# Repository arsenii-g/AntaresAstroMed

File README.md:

# AstroMed · Team Antares · NASA Space Apps 2026

An astronaut health monitoring prototype that brings sensor readings, guided daily checks, and explainable risk assessments together in one dashboard.

**Live demo:** [arsenii-g.github.io/AntaresAstroMed](https://arsenii-g.github.io/AntaresAstroMed/). Open the console from the landing page. The online version has no API behind it, so it replays a session recorded from the AstroMed API and the two-board simulator; daily checks are not saved there.

## About

AstroMed is developed by **Team Antares** for the NASA Space Apps 2026 challenge, *Create Health Monitoring Software for Astronauts on Space Missions*.

When medical support from Earth is delayed or unavailable, astronauts need a clear view of their condition and practical next steps. AstroMed connects an Arduino UNO and ESP32 sensor station to a web application that guides daily checks, explains risk alerts, and records exercise with physical sensors. Its goal is to support crew autonomy through understandable information and guidance.

This is the final hackathon version. The `main` branch contains the integrated application, firmware, simulator, and hardware design.

## What it does

- Collects crew and cabin telemetry, RFID check-ins, inactivity events, and exercise repetitions.
- Guides manual checks for blood pressure, fasting glucose, and mood.
- Evaluates four systems: cardiovascular, neurobehavioral, musculoskeletal, and cabin environment.
- Displays live readings, a clickable body view, explanations, recommendations, and trendlines with their measured data points.
- Prepares a summary for medical support on Earth when the overall risk reaches red.
- Includes firmware, a configurable two-ESP32 simulator, and KiCad schematic, PCB, BOM, and fabrication files.

## Run the API and web application

Use **Python 3.11 or later**. From the repository root, create a virtual environment:

```bash
python -m venv .venv
```

Activate it on macOS or Linux:

```bash
source .venv/bin/activate
```

On Windows PowerShell:

```powershell
.\.venv\Scripts\Activate.ps1
```

Install the dependencies and start the application:

```bash
python -m pip install -r requirements.txt
python -m uvicorn api.main:app --env-file .env.example --host 0.0.0.0 --port 8000
```

Open the [landing page](http://localhost:8000) or the [crew console](http://localhost:8000/console.html). The API also serves the frontend files, so no separate web server or frontend build is required. To connect from another device on the same network, replace `localhost` with the computer's local IP address.

The supplied [`.env.example`](.env.example) enables `ASTROMED_DEMO=1`, which triggers the inactivity alert after 30 seconds, matching the current firmware. Copy its settings to `.env` and start with `--env-file .env` to customize them.

Configuration uses `ASTROMED_API_KEY`, `ASTROMED_CORS_ORIGINS`, and the optional `ASTROMED_DATABASE_URL`. Legacy `SPACEHEALTH_*` names and an existing `spacehealth.db` are still honored; see [`api/README.md`](api/README.md) for details.

The default API key and the CORS `*` setting in `.env.example` are demo settings only; see the security notes in [`api/README.md`](api/README.md) before exposing the API beyond a trusted network.

The ESP32 must use the same API key as the backend and the computer's address in `API_BASE`. GET requests and the dashboard's manual check endpoint do not require an API key. See the [firmware setup and wiring guide](firmware/README.md) for the physical device.

## Try it with the simulator

With the API running, open another terminal, activate the virtual environment, and run:

```bash
python -m simulator.simulate
```

The simulator represents **two ESP32 devices, one per crew member**. Configure each crew member's target level in [`simulator/config.json`](simulator/config.json), or override it from the command line:

```bash
python -m simulator.simulate --level F3786E09=1 --level 336F8312=3
python -m simulator.simulate --mode normal
```

Manual checks are entered through the console's *Daily check* view. The simulator sends the same message format as the physical station; the API and risk engine calculate the assessments and trendlines. See the [simulator guide](simulator/README.md) for configuration and operating modes.

On Windows, after creating the virtual environment, [`start-demo.bat`](start-demo.bat) starts the API and simulator in separate windows.

## How it works

```mermaid
flowchart LR
    Sensors --> UNO[Arduino UNO]
    UNO -->|UART JSON| ESP[ESP32]
    ESP -->|Wi-Fi HTTP POST| API[FastAPI + SQLite]
    Web[AstroMed dashboard] -->|Daily check| API
    API -->|Local evaluate call| Risk[Rules engine]
    Risk -->|Assessment| API
    API -->|HTTP GET + WebSocket| Web
```

The physical station and simulator send telemetry every **2 seconds**. The API preserves the original UTC timestamps, handles duplicate retries, stores the messages in SQLite, and calls the risk engine in the same Python process.

The engine uses configurable, explainable rules in [`risk/thresholds.json`](risk/thresholds.json). It assigns levels from **0 (green)** to **3 (red)**, with a reason for each alert. Missing readings remain `null`: they mean **no data**, never a normal measurement.

The console follows RFID check-ins, allows manual crew selection, and shows the readings, system status, actions, and trendlines returned by the engine. The Earth summary is prepared for review and copying; it is not automatically sent to an external service.

### Hardware

An Arduino UNO reads the sensors and an ESP32 forwards the data over Wi-Fi. The custom PCB that combines them is designed in KiCad; see the [hardware guide](hardware/README.md).

## Repository structure

| Directory | Contents | Owner |
|---|---|---|
| `contracts/` | JSON examples and shared Pydantic models | Team Antares |
| `firmware/` | Arduino UNO sensor acquisition and ESP32 Wi-Fi gateway | [0xtherin](https://github.com/0xtherin) |
| `hardware/` | KiCad schematic, PCB layout, fabrication files, and BOM | Team Antares |
| `risk/` | Risk engine and `thresholds.json` | [arsenii-g](https://github.com/arsenii-g) |
| `simulator/` | Two simulated ESP32 devices with configurable levels | [arsenii-g](https://github.com/arsenii-g) |
| `api/` | FastAPI endpoints, SQLite persistence, and WebSocket | [arsenii-g](https://github.com/arsenii-g), [Pought79](https://github.com/Pought79) |
| `frontend/web/` | AstroMed console, clickable body, daily checks, and charts | [Pought79](https://github.com/Pought79) |

## Data contracts

| Contract | Flow | Interface | Owner |
|---|---|---|---|
| ① | Telemetry and events: ESP32 → API | `POST /api/v1/telemetry`, `POST /api/v1/events` | 0xtherin |
| ② | Manual check: frontend → API | `POST /api/v1/checks` | Pought79 |
| ③ | Risk assessment: engine → API | `evaluate(...)` | arsenii-g |
| ④ | Latest state and live updates: API → frontend | `GET /api/v1/crew/{crew_id}/latest`, WebSocket | arsenii-g, Pought79 |

All dates use UTC in ISO 8601 format. The API imports the engine directly:

```python
from datetime import datetime, timezone
from risk import evaluate

assessment = evaluate(
    telemetry=telemetry_messages,
    events=event_messages,
    manual_checks=manual_check_messages,
    now=datetime.now(timezone.utc),
)
```

Each input is a list of JSON message dictionaries for a **single `crew_id`**. The engine returns the assessment described in [`contracts/assessment.example.json`](contracts/assessment.example.json). Crew names and roles are provided by the API or frontend.

The API supplies telemetry from the last minute and events and manual checks from the last seven days. See the [risk engine guide](risk/README.md) for evaluation rules and trendlines, the [contract definitions](contracts/README.md) for message formats, and the [API guide](api/README.md) for endpoints.

## Run the checks

Install the development dependencies and run the Python suite:

```bash
python -m pip install -r requirements-dev.txt
python -m pytest -q
```

Frontend tests require **Node.js 20 or later**, with no additional packages:

```bash
node --test frontend/web/tests/*.test.js
```

## Final version and contributions

Use [`main`](https://github.com/arsenii-g/AntaresAstroMed/tree/main) for the final Team Antares submission. Historical feature branches are retained as development history; the integrated console served by the API is in `frontend/web/`.

For future changes, open a pull request against `main`. Changes to a data contract should be reviewed by both the producer and consumer of that data.

## Credits

AstroMed builds on the following third-party software, data, and standards.

- **Backend:** [FastAPI](https://fastapi.tiangolo.com/), [Uvicorn](https://www.uvicorn.org/), [SQLAlchemy](https://www.sqlalchemy.org/), and [Pydantic](https://docs.pydantic.dev/) (see `requirements.txt`). Tests use [pytest](https://pytest.org/) and [HTTPX](https://www.python-httpx.org/).
- **Firmware:** the Arduino and ESP32 cores, the [MFRC522](https://github.com/miguelbalboa/rfid) library for the RFID reader, and [ArduinoJson](https://arduinojson.org/).
- **Hardware design:** [KiCad](https://www.kicad.org/).
- **Frontend:** [Google Fonts](https://fonts.google.com/): Sora, Inter, and JetBrains Mono.
- **Standards and guidelines behind `risk/thresholds.json`:** NASA-STD-3001 (vols. 1 and 2), American Heart Association (AHA/ACC) blood pressure and heart rate guidance, American Diabetes Association (ADA) Standards of Care, and NOAA/NWS heat index tables.
- **Thermistor calibration:** the Steinhart-Hart coefficients in `firmware/tests/thermistor_test/` come from the Elegoo sensor kit tutorial.

## Use of AI (Super Intelligence tools)

As allowed by the NASA Space Apps rules, Team Antares used AI assistants, including Anthropic's Claude, during the hackathon. We disclose that use here.

- **Code:** AI-assisted. Parts of the API, risk engine, simulator, web console, firmware and tests were written, debugged or reviewed with AI help. The team designed the system, built and wired the hardware, and ran and checked the code against the real sensor station and the test suite.
- **Writing and translation:** AI-assisted. The documentation was drafted, edited and translated from Spanish to English with AI help.
- **Presentation and video:** AI-assisted. The motion graphics in the demo video were generated with AI-written code. The video carries a visible "SI-generated" watermark. Its footage of the breadboard and its voice-over are the team's own.
- **Hardware design files:** AI-assisted. The KiCad schematic and PCB files were prepared with AI help and checked with KiCad's electrical and design rule checks.
- **Not AI-generated:** the physical prototype, its wiring and the sensor readings recorded from it.

No NASA logos or other NASA branding were generated or modified.

## Limitations

AstroMed is an educational prototype built with a sensor kit. Its measurements are not medical-grade, and its thresholds are for demonstration rather than clinical use. Sources and assumptions are documented in `risk/thresholds.json`.

Sleep monitoring and respiration measurement are outside the current scope. The HC-SR04 is used to count push-ups. The four assessed systems are cardiovascular, neurobehavioral, musculoskeletal, and cabin environment.

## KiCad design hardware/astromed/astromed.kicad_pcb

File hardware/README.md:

# AstroMed · Team Antares: Arduino UNO + ESP32 shield

Schematic and PCB for the AstroMed shield, a board that replaces the breadboard prototype. It sits on top of an **Arduino UNO R3**, carries an **ESP32 DevKit V1 (30-pin, CP2102)** in female headers, and provides connectors for every sensor.

Pin assignments follow [`firmware/uno_sensors/config.h`](../firmware/uno_sensors/config.h), [`firmware/esp32_gateway/config.example.h`](../firmware/esp32_gateway/config.example.h) and [`firmware/README.md`](../firmware/README.md). Any pin change on the PCB must also be made in `config.h`.

The PIR sensor, the sleep sensors and the HC-SR04 respiration measurement were removed from the project and are not part of this design.

## Files

| File | Description |
|---|---|
| `schematic.pdf` | Schematic, A3 PDF |
| `schematic.png` | Schematic, PNG at 200 dpi |
| `bom.csv` | Bill of materials exported from KiCad |
| `astromed/astromed.kicad_pro` | KiCad project file |
| `astromed/astromed.kicad_sch` | Schematic (KiCad 10 format) |
| `astromed/astromed.net` | Netlist (KiCad S-expression) |
| `astromed/erc.rpt` | Electrical rules check report |
| `astromed/astromed.kicad_pcb` | PCB layout |
| `astromed/astromed.kicad_dru` | Custom design rules (see [PCB](#pcb)) |
| `astromed/drc.rpt` | Design rules check report, including schematic parity |
| `pcb_top.png`, `pcb_bottom.png`, `pcb_3d.png` | 3D renders of the board |
| `kicad_pcb_editor.png`, `kicad_3d_bottom.png` | Screenshots of the KiCad PCB editor and 3D viewer (bottom side) |
| `gerbers/` | Gerber and Excellon drill files |
| `astromed_gerbers.zip` | Same files zipped, ready to upload to a PCB manufacturer |

- **KiCad version:** 10.0.8. Files saved by KiCad 10 cannot be opened in KiCad 8 or 9.
- **Libraries:** only the standard KiCad libraries are used (`Device`, `Connector_Generic`, `MCU_Module`, `Switch`, `Jumper`, `power`). Symbols are also embedded in the `.kicad_sch` file.
- **Schematic changes:** after editing the schematic, run *Tools → Update PCB from Schematic* (F8) in the PCB editor. Footprints are linked to their symbols, so existing placement and routing are kept.

## Design notes

- **Shield form factor.** `A1` uses the `Module:Arduino_UNO_R3_WithMountingHoles` footprint, which provides the UNO outline, mounting holes and header positions. Use stackable headers (1x10, 2x 1x8 and 1x6).
- **Sensors that move use JST-XH connectors.** The HC-SR04 (on the floor, push-ups), the tilt switch (worn by the crew member), the NTC (wrist) and the pulse finger clip connect through latching 2.5 mm JST-XH connectors (`J2`, `J3`, `J6`, `J7`), so cables do not pull out during use.
- **Static modules plug into the board.** The DHT11 (`J4`) and the DS1307 RTC (`J5`) plug into female sockets, with no cables. The RC522 (`J1`) stays on a 1x08 male header and is wired to the reader, which must sit on an accessible face of the enclosure.
- **ESP32 on 1x15 female headers, with two positions for the right row.** KiCad has no symbol for the DevKit V1. Pin 1 of each header is at the antenna end. The right row can be fitted at 25.4 mm (`J9`, row A, default) or 22.86 mm (`J11`, row B, marked DNP) from the left row (`J8`), because 30-pin DevKit V1 clones use either spacing. Measure the board and solder the socket in the matching row only.
- **Pulse sensor on a 4-pin connector (`J7`).** The LED and LDR face each other across the fingertip, so they are mounted in an external finger clip. The 220 Ω and 10 kΩ resistors are on the PCB. The firmware measures the pulse with this LED and LDR pair over a 10 s window (`PIN_PULSE_LED`, `PIN_PULSE_LDR` and `PULSE_WINDOW_MS` in `config.h`).
- **Off-board parts.** `TH1` (NTC), `D1` (LED), `R6` (LDR) and `SW2` (tilt switch) are drawn to show the complete circuit and are listed in the BOM. They are marked `on_board = no` (field *Mounting*), so they have no footprint and are not transferred to the PCB. Each one is wired to its connector.
- **Push button `SW1`.** 6 mm tactile switch mounted on the board. It is optional.
- **Spare pins.** D2, A2 and A3 are routed to header `J10` together with 5V and GND.

## Connections

### Arduino UNO

| UNO pin | Net | Connects to |
|---|---|---|
| D1 (TX) | `UNO_TX` | R4 1 kΩ to `ESP_RX2` (level divider to the ESP32) |
| D2 | `D2_SPARE` | J10-1 (spare) |
| D3 | `D3_TILT` | J3-1, SW-520D tilt switch to GND (internal pull-up) |
| D4 | `D4_DHT` | J4-1 (DHT11 data) |
| D5 | `D5_US_TRIG` | J2-2 (HC-SR04 TRIG) |
| D6 | `D6_US_ECHO` | J2-3 (HC-SR04 ECHO) |
| D7 | `D7_BTN` | SW1 to GND (internal pull-up) |
| D8 | `D8_PULSE_LED` | R2 220 Ω to `PULSE_LED_A`, J7-1 (LED anode) |
| D9 | `D9_RFID_RST` | J1-7 (RC522 RST) |
| D10 | `D10_RFID_SS` | J1-1 (RC522 SDA/SS) |
| D11 | `D11_SPI_MOSI` | J1-3 (MOSI) |
| D12 | `D12_SPI_MISO` | J1-4 (MISO) |
| D13 | `D13_SPI_SCK` | J1-2 (SCK) |
| A0 | `A0_NTC` | J6-2 (NTC to 5V), R1 10 kΩ to GND |
| A1 | `A1_PULSE_LDR` | J7-4 (LDR to 5V), R3 10 kΩ to GND |
| A2 | `A2_SPARE` | J10-2 (spare) |
| A3 | `A3_SPARE` | J10-3 (spare) |
| A4 (SDA) | `A4_I2C_SDA` | J5-3 (DS1307 SDA) |
| A5 (SCL) | `A5_I2C_SCL` | J5-4 (DS1307 SCL) |
| 5V | `+5V` | J2-1, J4-2, J5-1, J6-1, J7-3, J10-4, JP1-1 |
| 3.3V | `+3V3` | J1-8 only (RC522 supply) |
| GND (x3) | `GND` | Common ground, including the ESP32 |

Not connected: D0/RX (used by USB for programming), VIN, RESET, IOREF, AREF, and the SDA/SCL pins next to AREF (internally the same as A4/A5).

### Connectors

| Ref | Function | Pin 1 | Pin 2 | Pin 3 | Pin 4 | Pin 5 | Pin 6 | Pin 7 | Pin 8 |
|---|---|---|---|---|---|---|---|---|---|
| J1 (1x08) | RC522 | SDA (D10) | SCK (D13) | MOSI (D11) | MISO (D12) | IRQ (NC) | GND | RST (D9) | 3.3V |
| J2 (JST-XH 4) | HC-SR04 (floor, push-ups) | VCC 5V | TRIG (D5) | ECHO (D6) | GND | | | | |
| J3 (JST-XH 2) | SW-520D (worn by crew member) | D3 | GND | | | | | | |
| J4 (socket 1x03) | DHT11 module | DATA (D4) | 5V | GND | | | | | |
| J5 (socket 1x04) | DS1307 RTC | VCC 5V | GND | SDA (A4) | SCL (A5) | | | | |
| J6 (JST-XH 2) | 10k NTC (skin contact) | 5V | A0 | | | | | | |
| J7 (JST-XH 4) | Pulse finger clip | LED anode (after 220 Ω) | LED cathode (GND) | LDR to 5V | LDR to A1 | | | | |
| J10 (1x05) | Spare pins | D2 | A2 | A3 | 5V | GND | | | |
| JP1 (1x02 + jumper) | ESP32 power | UNO 5V | ESP32 VIN | | | | | | |

The DHT11 and RTC sockets follow the pin order above, which may not match every module: pinouts vary between manufacturers. Check the module before plugging it in. If the order differs, connect it with jumper wires by pin name instead.

### ESP32 DevKit V1

J8 is the left row and J9 the right row (row A, 25.4 mm), with pin 1 at the antenna end. J11 (row B, 22.86 mm) has the same pinout as J9.

| Pin | J8 | Connection | J9 | Connection |
|---|---|---|---|---|
| 1 | EN | NC | D23 | NC |
| 2 | VP (GPIO36) | NC | D22 | NC |
| 3 | VN (GPIO39) | NC | TX0 | NC |
| 4 | D34 | NC | RX0 | NC |
| 5 | D35 | NC | D21 | NC |
| 6 | D32 | NC | D19 | NC |
| 7 | D33 | NC | D18 | NC |
| 8 | D25 | NC | D5 | NC |
| 9 | D26 | NC | TX2 (GPIO17) | NC |
| 10 | D27 | NC | **RX2 (GPIO16)** | **`ESP_RX2`** |
| 11 | D14 | NC | D4 | NC |
| 12 | D12 | NC | D2 | NC (on-board blue LED) |
| 13 | D13 | NC | D15 | NC |
| 14 | **GND** | **GND** | **GND** | **GND** |
| 15 | **VIN** | **`ESP_VIN`** (JP1) | 3V3 | NC |

### UART link, UNO to ESP32 (115200 baud)

```
UNO D1 (TX) ──R4 1k──┬── ESP32 GPIO16 (RX2)     5 V × 2k/(1k+2k) = 3.33 V
                     └──R5 2k── GND
```

- The link is one-way. ESP32 TX2 is not connected.
- With JP1 fitted, the ESP32 is powered from the UNO 5V rail through VIN. With JP1 removed, the ESP32 is powered from its own USB port. Ground is shared in both cases.
- With JP1 removed and the ESP32 unpowered, the divider still applies about 3.3 V to GPIO16. This does not damage the board, but both boards should normally be powered together.

### Analog circuits

- **Body temperature:** 5V, NTC (via J6, on the crew member's wrist), A0, R1 10 kΩ, GND.
- **Pulse emitter:** D8, R2 220 Ω, red LED (via J7), GND.
- **Pulse receiver:** 5V, LDR (via J7), A1, R3 10 kΩ, GND.

## Bill of materials

| Ref | Qty | Part | KiCad footprint | Mounting |
|---|---|---|---|---|
| A1 | 1 | Arduino UNO R3 (host board) | `Module:Arduino_UNO_R3_WithMountingHoles` | Long-pin or stackable headers |
| - | 1 | ESP32 DevKit V1, 30-pin, CP2102 | (on J8/J9) | Plugged into headers |
| - | 1 set | Stackable headers for the UNO: 1x10, 2x 1x8, 1x6 | (on A1) | On board |
| J8, J9 | 2 | Female header 1x15, 2.54 mm | `Connector_PinSocket_2.54mm:PinSocket_1x15_P2.54mm_Vertical` | On board |
| J11 | - | Female header 1x15, 2.54 mm, instead of J9 for 22.86 mm boards | Same as above | DNP |
| J1 | 1 | Male header 1x08, 2.54 mm (RC522) | `Connector_PinHeader_2.54mm:PinHeader_1x08_P2.54mm_Vertical` | On board |
| J2, J7 | 2 | JST-XH B4B-XH-A, 4 pins (HC-SR04, pulse) | `Connector_JST:JST_XH_B4B-XH-A_1x04_P2.50mm_Vertical` | On board |
| J3, J6 | 2 | JST-XH B2B-XH-A, 2 pins (tilt, NTC) | `Connector_JST:JST_XH_B2B-XH-A_1x02_P2.50mm_Vertical` | On board |
| - | 2 + 2 | JST-XH housings XHP-4 and XHP-2, with SXH-001T-P0.6 crimp terminals | - | Cable side |
| J4 | 1 | Female socket 1x03, 2.54 mm (DHT11) | `Connector_PinSocket_2.54mm:PinSocket_1x03_P2.54mm_Vertical` | On board |
| J5 | 1 | Female socket 1x04, 2.54 mm (RTC) | `Connector_PinSocket_2.54mm:PinSocket_1x04_P2.54mm_Vertical` | On board |
| J10 | 1 | Male header 1x05, 2.54 mm (spare pins) | `Connector_PinHeader_2.54mm:PinHeader_1x05_P2.54mm_Vertical` | On board |
| JP1 | 1 | Male header 1x02 with jumper | `Connector_PinHeader_2.54mm:PinHeader_1x02_P2.54mm_Vertical` | On board |
| R1, R3 | 2 | Resistor 10 kΩ, 1/4 W | `Resistor_THT:R_Axial_DIN0207_L6.3mm_D2.5mm_P10.16mm_Horizontal` | On board |
| R2 | 1 | Resistor 220 Ω, 1/4 W | Same as above | On board |
| R4 | 1 | Resistor 1 kΩ, 1/4 W | Same as above | On board |
| R5 | 1 | Resistor 2 kΩ, 1/4 W (2.2 kΩ also acceptable, 3.4 V) | Same as above | On board |
| SW1 | 1 | Tactile switch 6x6 mm (optional) | `Button_Switch_THT:SW_PUSH_6mm` | On board |
| TH1 | 1 | NTC thermistor 10 kΩ | - | Off board, wired to J6 |
| D1 | 1 | Red LED 5 mm | - | Off board, wired to J7 |
| R6 | 1 | Photoresistor (LDR, e.g. GL5528) | - | Off board, wired to J7 |
| SW2 | 1 | SW-520D tilt switch | - | Off board, wired to J3 |
| - | 1 | RC522 module with cards | - | Wired to J1 |
| - | 1 | HC-SR04 module | - | Wired to J2 (floor-mounted) |
| - | 1 | DHT11 module (3-pin) | - | Plugged into J4 |
| - | 1 | DS1307 RTC module | - | Plugged into J5 |

The KiCad export is in `bom.csv`.

## PCB

| Parameter | Value |
|---|---|
| Size | 104.14 x 67.31 mm (UNO outline plus a 35.56 mm extension for the ESP32 and a 13.97 mm connector strip) |
| Layers | 2, 1.6 mm FR-4, all parts through-hole |
| Tracks | 0.3 mm signals, 0.5 mm for +5V, +3V3 and ESP_VIN |
| Clearance | 0.2 mm minimum, 0.6 mm from tracks to the board edge |
| Vias | 0.7 mm pad, 0.35 mm drill (10 in total) |
| Ground | GND pour on both layers |
| Mounting | The four UNO holes plus one M3 hole (`H1`) under the overhanging corner |

Layout:

- The UNO headers are at their standard positions on the left. The ESP32 sits on the right extension with its USB connector towards the bottom edge. Its antenna overhangs the top edge, over a copper keepout area.
- All cable connectors are in a row along the bottom edge, labelled on the silkscreen (`J4 DHT11`, `J1 RC522`, `J2 HC-SR04`, `J3 TILT`, `J6 NTC`, `J7 PULSE`). The DHT11 is in the far corner, away from the heat of the ESP32.
- The divider resistors R4 and R5 sit under the ESP32, between its two rows. With the socket height, they fit under the module.
- The UNO USB-B connector is close to the underside of the shield. Put a piece of insulating tape on top of it before stacking the boards.

`astromed.kicad_dru` adds five rules for situations that are intended in this design: shield parts inside the UNO courtyard, the overlapping J9/J11 rows and their silkscreen, the UNO outline reaching past the board edge, and GND pads with a single thermal spoke on the top layer, which are still fully connected on the bottom layer.

Screenshots from KiCad:

To order the board, upload `astromed_gerbers.zip`. Default options are fine: 2 layers, 1.6 mm, 1 oz copper, any solder mask colour.

## Verification

- **ERC:** `kicad-cli sch erc --severity-all` reports 0 errors and 0 warnings. A single `PWR_FLAG` is placed on GND; +5V and 3V3 are driven by the UNO power pins.
- **Netlist:** all 25 named nets were checked against the connection tables above, including off-board parts.
- **Footprints:** every footprint in the netlist loads in KiCad 10.0.8 `pcbnew`, and pad counts match the symbol pin counts (32 for the UNO).
- **DRC:** `kicad-cli pcb drc --schematic-parity --severity-all --refill-zones` reports 0 violations, 0 unconnected pads and 0 schematic parity errors.
- **Not yet done:** measurement of the ESP32 row spacing (choose J9 or J11), and fabrication and testing of a board.

## Regenerating outputs

From `hardware/`, with `kicad-cli` from KiCad 10:

```bash
kicad-cli sch erc --severity-all -o astromed/erc.rpt astromed/astromed.kicad_sch
kicad-cli sch export netlist -o astromed/astromed.net astromed/astromed.kicad_sch
kicad-cli sch export bom --fields 'Reference,Value,Footprint,${QUANTITY},Mounting,${DNP}' --labels 'Reference,Value,Footprint,Quantity,Mounting,DNP' --group-by Value,Footprint --ref-range-delimiter '' -o bom.csv astromed/astromed.kicad_sch
kicad-cli sch export pdf -o schematic.pdf astromed/astromed.kicad_sch
pdftoppm -png -r 200 -singlefile schematic.pdf schematic
kicad-cli pcb drc --schematic-parity --severity-all --refill-zones --save-board -o astromed/drc.rpt astromed/astromed.kicad_pcb
kicad-cli pcb export gerbers --no-protel-ext -l F.Cu,B.Cu,F.Silkscreen,B.Silkscreen,F.Mask,B.Mask,Edge.Cuts -o gerbers/ astromed/astromed.kicad_pcb
kicad-cli pcb export drill --excellon-separate-th -o gerbers/ astromed/astromed.kicad_pcb
(cd gerbers && zip ../astromed_gerbers.zip *)
kicad-cli pcb render --side top --quality high -o pcb_top.png astromed/astromed.kicad_pcb
```

When using the AppImage, run `kicad-cli` as `./kicad.appimage kicad-cli <arguments>`.

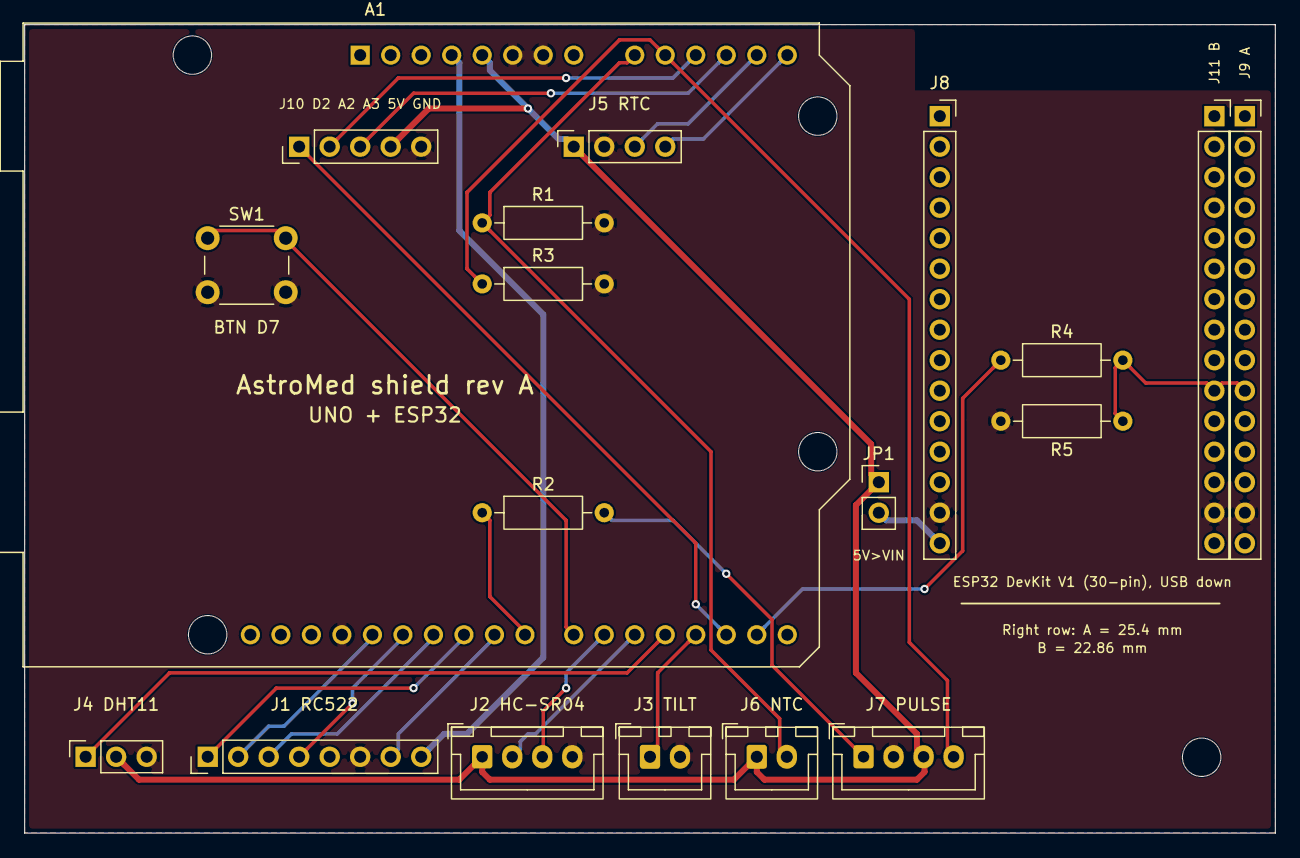
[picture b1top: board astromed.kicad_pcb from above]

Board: 2 copper layers, 104.1 x 67.3 mm, 20 parts (0 on the bottom side), 25 nets.

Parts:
A1: Arduino_UNO_R3; Arduino_UNO_R3_WithMountingHoles
H1: M3; MountingHole_3.2mm_M3
J1: RC522; PinHeader_1x08_P2.54mm_Vertical
J2: HC-SR04; JST_XH_B4B-XH-A_1x04_P2.50mm_Vertical
J3: TILT; JST_XH_B2B-XH-A_1x02_P2.50mm_Vertical
J4: DHT11; PinSocket_1x03_P2.54mm_Vertical
J5: RTC_DS1307; PinSocket_1x04_P2.54mm_Vertical
J6: NTC; JST_XH_B2B-XH-A_1x02_P2.50mm_Vertical
J7: PULSE; JST_XH_B4B-XH-A_1x04_P2.50mm_Vertical
J8: ESP32_LEFT; PinSocket_1x15_P2.54mm_Vertical
J9: ESP32_RIGHT; PinSocket_1x15_P2.54mm_Vertical
J10: SPARE; PinHeader_1x05_P2.54mm_Vertical
J11: ESP32_RIGHT_ALT; PinSocket_1x15_P2.54mm_Vertical
JP1: 5V->VIN; PinHeader_1x02_P2.54mm_Vertical
R1, R3: 10k; R_Axial_DIN0207_L6.3mm_D2.5mm_P10.16mm_Horizontal
R2: 220; R_Axial_DIN0207_L6.3mm_D2.5mm_P10.16mm_Horizontal
R4: 1k; R_Axial_DIN0207_L6.3mm_D2.5mm_P10.16mm_Horizontal
R5: 2k; R_Axial_DIN0207_L6.3mm_D2.5mm_P10.16mm_Horizontal
SW1: Push button 6 mm; SW_PUSH_6mm

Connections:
+3V3: A1.4, J1.8
+5V: A1.5, J2.1, J4.2, J5.1, J6.1, J7.3, J10.4, JP1.1
A0_NTC: A1.9, J6.2, R1.1
A1_PULSE_LDR: A1.10, J7.4, R3.1
A2_SPARE: A1.11, J10.2
A3_SPARE: A1.12, J10.3
A4_I2C_SDA: A1.13, J5.3
A5_I2C_SCL: A1.14, J5.4
D2_SPARE: A1.17, J10.1
D3_TILT: A1.18, J3.1
D4_DHT: A1.19, J4.1
D5_US_TRIG: A1.20, J2.2
D6_US_ECHO: A1.21, J2.3
D7_BTN: A1.22, SW1.1
D8_PULSE_LED: A1.23, R2.1
D9_RFID_RST: A1.24, J1.7
D10_RFID_SS: A1.25, J1.1
D11_SPI_MOSI: A1.26, J1.3
D12_SPI_MISO: A1.27, J1.4
D13_SPI_SCK: A1.28, J1.2
ESP_RX2: J9.10, J11.10, R4.2, R5.1
ESP_VIN: J8.15, JP1.2
GND: A1.6, A1.7, A1.29, J1.6, J2.4, J3.2, J4.3, J5.2, J7.2, J8.14, J9.14, J10.5, J11.14, R1.2, R3.2, R5.2, SW1.2
PULSE_LED_A: J7.1, R2.2
UNO_TX: A1.16, R4.1

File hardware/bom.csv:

"Reference","Value","Footprint","Quantity","Mounting","DNP"
"A1","Arduino_UNO_R3","Module:Arduino_UNO_R3_WithMountingHoles","1","",""
"D1","Red LED 5 mm","","1","Off board (wired to its connector)",""
"J1","RC522","Connector_PinHeader_2.54mm:PinHeader_1x08_P2.54mm_Vertical","1","",""
"J2","HC-SR04","Connector_JST:JST_XH_B4B-XH-A_1x04_P2.50mm_Vertical","1","",""
"J3","TILT","Connector_JST:JST_XH_B2B-XH-A_1x02_P2.50mm_Vertical","1","",""
"J4","DHT11","Connector_PinSocket_2.54mm:PinSocket_1x03_P2.54mm_Vertical","1","",""
"J5","RTC_DS1307","Connector_PinSocket_2.54mm:PinSocket_1x04_P2.54mm_Vertical","1","",""
"J6","NTC","Connector_JST:JST_XH_B2B-XH-A_1x02_P2.50mm_Vertical","1","",""
"J7","PULSE","Connector_JST:JST_XH_B4B-XH-A_1x04_P2.50mm_Vertical","1","",""
"J8","ESP32_LEFT","Connector_PinSocket_2.54mm:PinSocket_1x15_P2.54mm_Vertical","1","",""
"J9","ESP32_RIGHT","Connector_PinSocket_2.54mm:PinSocket_1x15_P2.54mm_Vertical","1","",""
"J10","SPARE","Connector_PinHeader_2.54mm:PinHeader_1x05_P2.54mm_Vertical","1","",""
"J11","ESP32_RIGHT_ALT","Connector_PinSocket_2.54mm:PinSocket_1x15_P2.54mm_Vertical","1","","DNP"
"JP1","5V->VIN","Connector_PinHeader_2.54mm:PinHeader_1x02_P2.54mm_Vertical","1","",""
"R1,R3","10k","Resistor_THT:R_Axial_DIN0207_L6.3mm_D2.5mm_P10.16mm_Horizontal","2","",""
"R2","220","Resistor_THT:R_Axial_DIN0207_L6.3mm_D2.5mm_P10.16mm_Horizontal","1","",""
"R4","1k","Resistor_THT:R_Axial_DIN0207_L6.3mm_D2.5mm_P10.16mm_Horizontal","1","",""
"R5","2k","Resistor_THT:R_Axial_DIN0207_L6.3mm_D2.5mm_P10.16mm_Horizontal","1","",""
"R6","LDR GL5528","","1","Off board (wired to its connector)",""
"SW1","Push button 6 mm","Button_Switch_THT:SW_PUSH_6mm","1","",""
"SW2","SW-520D","","1","Off board (wired to its connector)",""
"TH1","NTC 10k","","1","Off board (wired to its connector)",""
